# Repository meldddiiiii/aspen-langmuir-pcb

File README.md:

# Single Langmuir Probe PCB

KiCad redesign of the USC ASPEN single Langmuir probe sweep board, for the Fall 2026 ASPEN PCB competition.

An OPA454 high-voltage op-amp amplifies a triangle-wave sweep to about ±35 V to bias the probe. Probe current is measured across a 100 Ω shunt by an INA149 high-common-mode difference amplifier, which outputs a ground-referenced signal safe for an NI USB-6211 DAQ.

## Key changes from the original

- Feedback resistors scaled to 2 kΩ / 5.1 kΩ (same 3.55 gain, 5 mA instead of 5 A)
- 100 pF feedback capacitor for bandwidth limiting and stability
- Correct OPA454 symbol, enable pull-up, and thermal pad tied to V−
- Decoupling and bulk capacitors on every supply
- INA149 current sense, powered by an on-board ±12 V zener supply
- Solid ground plane, V− thermal island, HV net class with 0.6 mm clearance

Full reasoning and math: [DESIGN_NOTES.md](DESIGN_NOTES.md)

## Files

- `LangmuirProbePCB_v2_opa454.kicad_pro` — open this in KiCad 10
- `.kicad_sch` / `.kicad_pcb` — schematic and board
- Custom symbol and footprint libraries are in this folder

Designed by Melodie Peng.

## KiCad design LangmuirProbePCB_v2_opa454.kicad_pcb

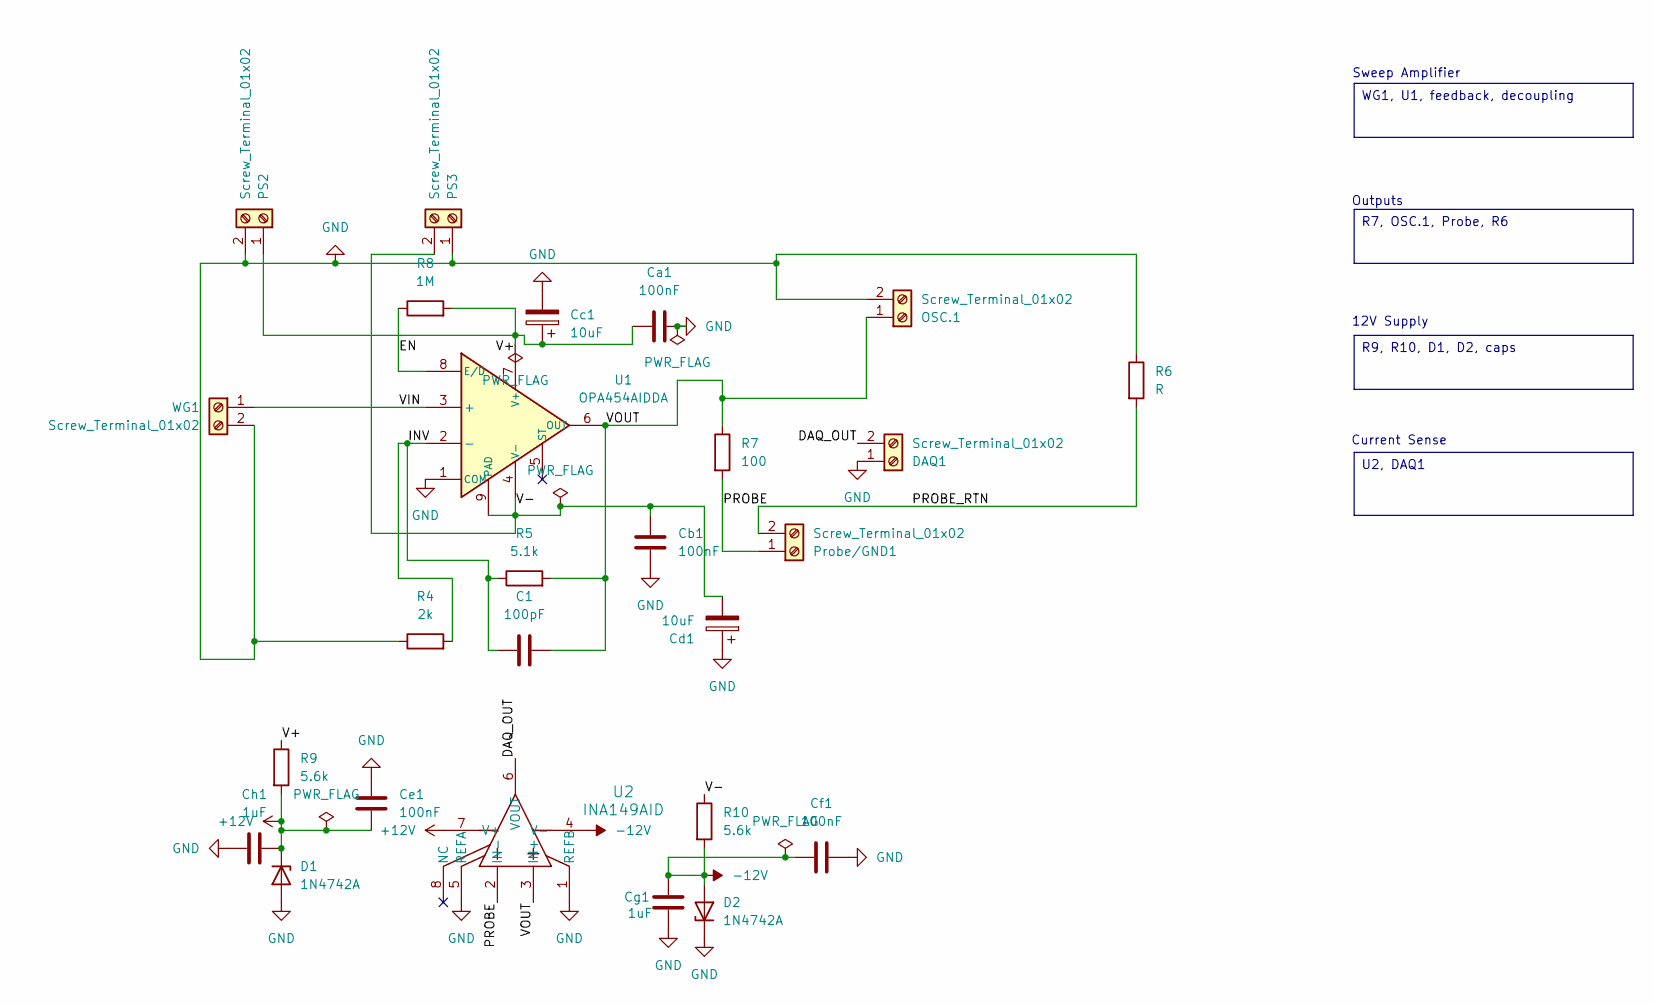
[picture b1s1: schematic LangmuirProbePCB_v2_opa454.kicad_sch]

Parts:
C1: 100pF; C_Disc_D5.0mm_W2.5mm_P5.00mm
Ca1: 100nF; C_Disc_D5.0mm_W2.5mm_P5.00mm
Cb1: 100nF; C_Disc_D5.0mm_W2.5mm_P5.00mm
Cc1: 10uF; CP_Radial_D6.3mm_P2.50mm
Cd1: 10uF; CP_Radial_D6.3mm_P2.50mm
Ce1: 100nF; C_Disc_D5.0mm_W2.5mm_P5.00mm
Cf1: 100nF; C_Disc_D5.0mm_W2.5mm_P5.00mm
Cg1: 1uF; C_Disc_D5.0mm_W2.5mm_P5.00mm
Ch1: 1uF; C_Disc_D5.0mm_W2.5mm_P5.00mm
D1, D2: 1N4742A; D_DO-41_SOD81_P10.16mm_Horizontal
DAQ1: Screw_Terminal_01x02; TerminalBlock_Phoenix_MPT-0,5-2-2.54_1x02_P2.54mm_Horizontal
OSC.1: Screw_Terminal_01x02; TerminalBlock_Phoenix_MPT-0,5-2-2.54_1x02_P2.54mm_Horizontal
PS2, PS3: Screw_Terminal_01x02; TerminalBlock_Phoenix_MPT-0,5-2-2.54_1x02_P2.54mm_Horizontal
Probe/GND1: Screw_Terminal_01x02; TerminalBlock_Phoenix_MPT-0,5-2-2.54_1x02_P2.54mm_Horizontal
R4: 2k; R_Axial_DIN0207_L6.3mm_D2.5mm_P10.16mm_Horizontal
R5: 5.1k; R_Axial_DIN0207_L6.3mm_D2.5mm_P10.16mm_Horizontal
R6: R; R_Axial_DIN0207_L6.3mm_D2.5mm_P10.16mm_Horizontal
R7: 100; R_Axial_DIN0411_L9.9mm_D3.6mm_P12.70mm_Horizontal
R8: 1M; R_Axial_DIN0207_L6.3mm_D2.5mm_P10.16mm_Horizontal
R9, R10: 5.6k; R_Axial_DIN0207_L6.3mm_D2.5mm_P10.16mm_Horizontal
U1: OPA454AIDDA; DDA0008J_NV
U2: INA149AID; SOIC-8_3.9x4.9mm_P1.27mm
WG1: Screw_Terminal_01x02; TerminalBlock_Phoenix_MPT-0,5-2-2.54_1x02_P2.54mm_Horizontal

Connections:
+12V: Ce1.2, Ch1.2, D1.1 (K), R9.2, U2.7 (V+)
-12V: Cf1.1, Cg1.2, D2.2 (A), R10.2, U2.4 (V-)
/DAQ_OUT: DAQ1.2, U2.6 (VOUT)
/EN: R8.1, U1.8 (E/D)
/INV: C1.2, R4.2, R5.1, U1.2 (-)
/PROBE: Probe/GND1.1, R7.2, U2.2 (IN-)
/PROBE_RTN: Probe/GND1.2, R6.2
/V+: Ca1.1, Cc1.1, PS2.1, R8.2, R9.1, U1.7 (V+)
/V-: Cb1.1, Cd1.2, PS3.2, R10.1, U1.4 (V-), U1.9 (PAD)
/VIN: U1.3 (+), WG1.1
/VOUT: C1.1, OSC.1.1, R5.2, R7.1, U1.6 (OUT), U2.3 (IN+)
GND: Ca1.2, Cb1.2, Cc1.2, Cd1.1, Ce1.1, Cf1.2, Cg1.1, Ch1.1, D1.2 (A), D2.1 (K), DAQ1.1, OSC.1.2, PS2.2, PS3.1, R4.1, R6.1, U1.1 (COM), U2.1 (REFB), U2.5 (REFA), WG1.2

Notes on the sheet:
Current Sense
12V Supply
Outputs
Sweep Amplifier
R9, R10, D1, D2, caps
U2, DAQ1
WG1, U1, feedback, decoupling
R7, OSC.1, Probe, R6

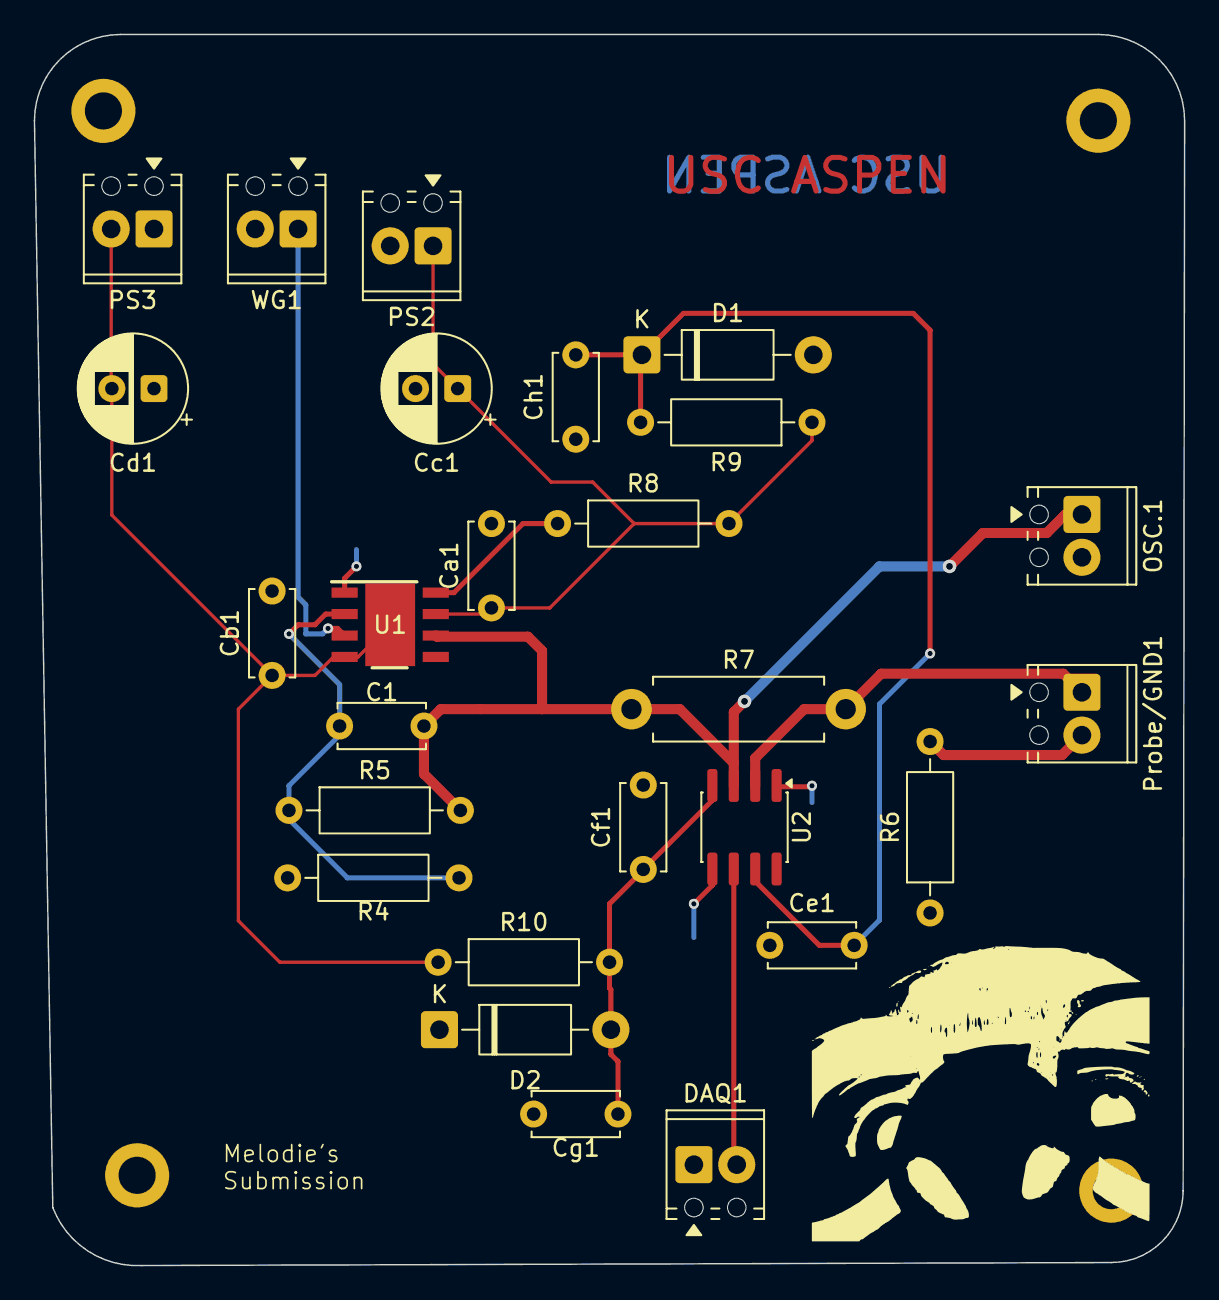
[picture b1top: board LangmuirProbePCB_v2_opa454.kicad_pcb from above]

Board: 2 copper layers, 68.2 x 73.0 mm, 26 parts (0 on the bottom side), 12 nets.
